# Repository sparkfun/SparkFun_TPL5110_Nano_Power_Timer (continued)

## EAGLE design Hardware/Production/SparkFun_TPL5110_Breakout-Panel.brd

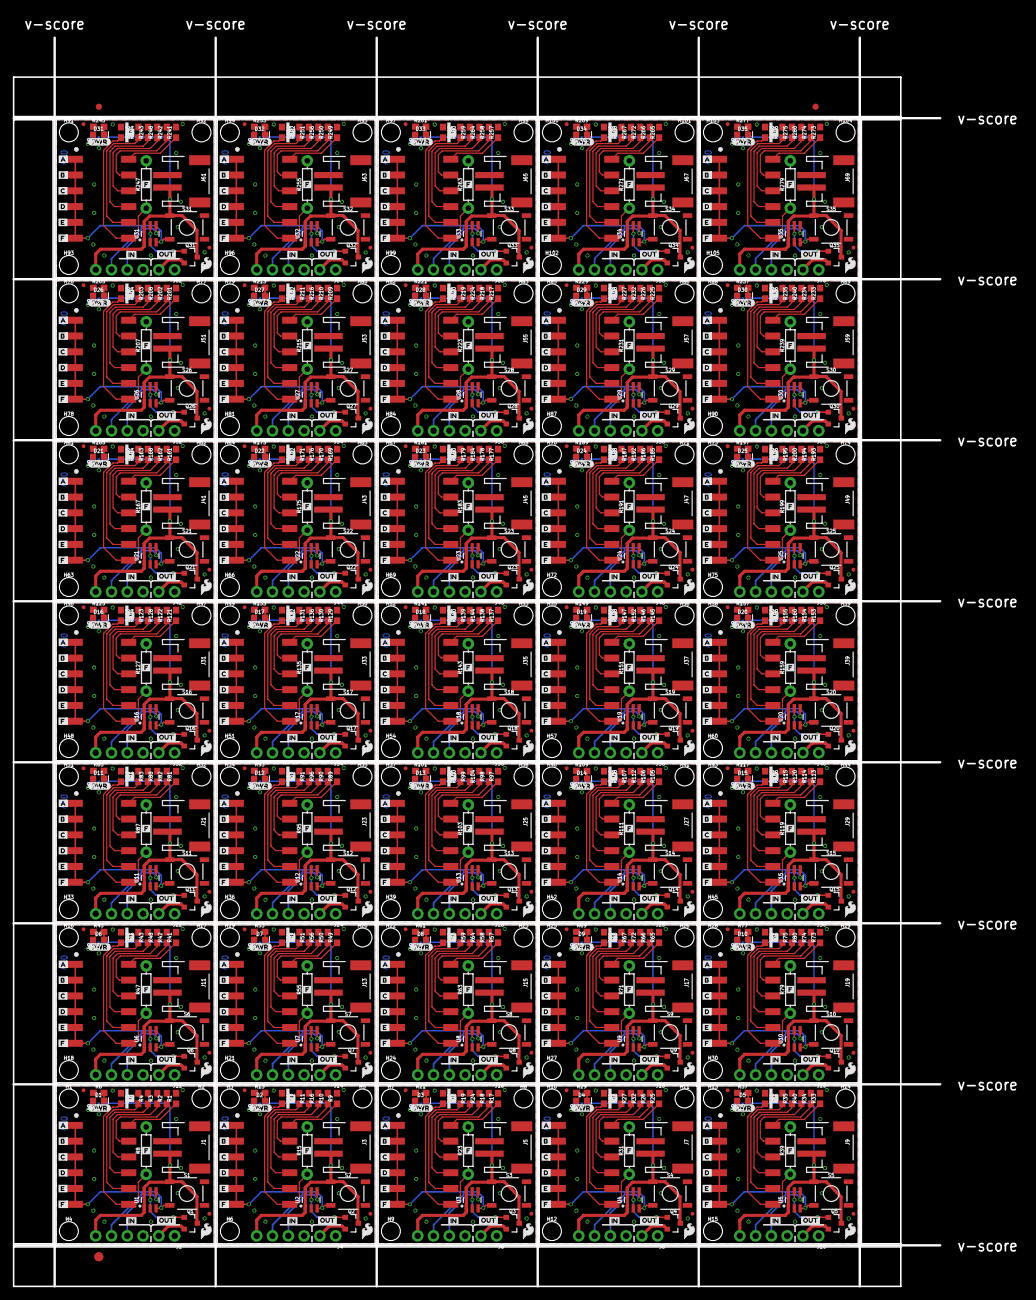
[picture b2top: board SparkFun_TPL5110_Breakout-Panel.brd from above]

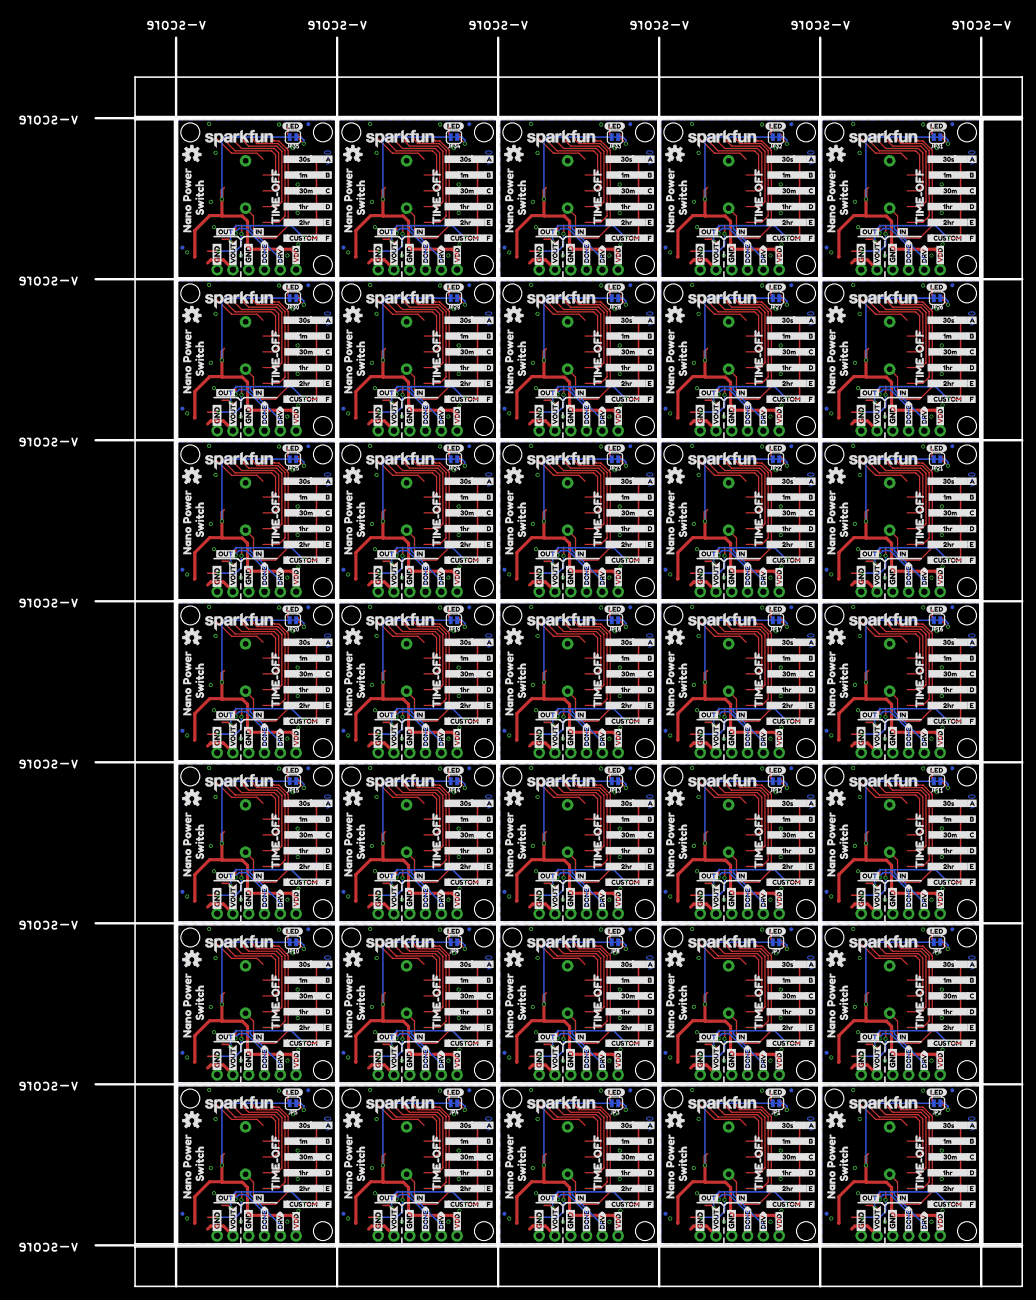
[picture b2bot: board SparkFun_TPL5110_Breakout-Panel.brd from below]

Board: 2 copper layers, 149.1 x 200.9 mm, 2138 parts (1015 on the bottom side), 490 nets.

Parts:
D1, D2, D3, D4, D5, D6, D7, D8, D9, D10, D11, D12, D13, D14, D15, D16, D17, D18, D19, D20, D21, D22, D23, D24, D25, D26, D27, D28, D29, D30, D31, D32, D33, D34, D35: RED; LED-0603
E$1, E$2: FIDUCIAL-1X2
E$3: FIDUCIAL-1.5X3
FD1, FD2, FD3, FD4, FD5, FD6, FD7, FD8, FD9, FD10, FD11, FD12, FD13, FD14, FD15, FD16, FD17, FD18, FD19, FD20, FD21, FD22, FD23, FD24, FD25, FD26, FD27, FD28, FD29, FD30, FD31, FD32, FD33, FD34, FD35, FD36, FD37, FD38, FD39, FD40, FD41, FD42, FD43, FD44, FD45, FD46, FD47, FD48, FD49, FD50, FD51, FD52, FD53, FD54, FD55, FD56, FD57, FD58, FD59, FD60, FD61, FD62, FD63, FD64, FD65, FD66, FD67, FD68, FD69, FD70, FD71, FD72, FD73, FD74, FD75, FD76, FD77, FD78, FD79, FD80, FD81, FD82, FD83, FD84, FD85, FD86, FD87, FD88, FD89, FD90, FD91, FD92, FD93, FD94, FD95, FD96, FD97, FD98, FD99, FD100, FD101, FD102, FD103, FD104, FD105, FD106, FD107, FD108, FD109, FD110, FD111, FD112, FD113, FD114, FD115, FD116, FD117, FD118, FD119, FD120, FD121, FD122, FD123, FD124, FD125, FD126, FD127, FD128, FD129, FD130, FD131, FD132, FD133, FD134, FD135, FD136, FD137, FD138, FD139, FD140: FIDUCIALUFIDUCIAL; FIDUCIAL-MICRO
H1, H2, H3, H4, H5, H6, H7, H8, H9, H10, H11, H12, H13, H14, H15, H16, H17, H18, H19, H20, H21, H22, H23, H24, H25, H26, H27, H28, H29, H30, H31, H32, H33, H34, H35, H36, H37, H38, H39, H40, H41, H42, H43, H44, H45, H46, H47, H48, H49, H50, H51, H52, H53, H54, H55, H56, H57, H58, H59, H60, H61, H62, H63, H64, H65, H66, H67, H68, H69, H70, H71, H72, H73, H74, H75, H76, H77, H78, H79, H80, H81, H82, H83, H84, H85, H86, H87, H88, H89, H90, H91, H92, H93, H94, H95, H96, H97, H98, H99, H100, H101, H102, H103, H104, H105: STAND-OFFTIGHT; STAND-OFF-TIGHT
J1, J3, J5, J7, J9, J11, J13, J15, J17, J19, J21, J23, J25, J27, J29, J31, J33, J35, J37, J39, J41, J43, J45, J47, J49, J51, J53, J55, J57, J59, J61, J63, J65, J67, J69: JST-2-SMD
J2, J4, J6, J8, J10, J12, J14, J16, J18, J20, J22, J24, J26, J28, J30, J32, J34, J36, J38, J40, J42, J44, J46, J48, J50, J52, J54, J56, J58, J60, J62, J64, J66, J68, J70: 1X06_NO_SILK
JP1, JP2, JP3, JP4, JP5, JP6, JP7, JP8, JP9, JP10, JP11, JP12, JP13, JP14, JP15, JP16, JP17, JP18, JP19, JP20, JP21, JP22, JP23, JP24, JP25, JP26, JP27, JP28, JP29, JP30, JP31, JP32, JP33, JP34, JP35: LED; SMT-JUMPER_2_NC_TRACE_SILK
LOGO1, LOGO4, LOGO7, LOGO10, LOGO13, LOGO16, LOGO19, LOGO22, LOGO25, LOGO28, LOGO31, LOGO34, LOGO37, LOGO40, LOGO43, LOGO46, LOGO49, LOGO52, LOGO55, LOGO58, LOGO61, LOGO64, LOGO67, LOGO70, LOGO73, LOGO76, LOGO79, LOGO82, LOGO85, LOGO88, LOGO91, LOGO94, LOGO97, LOGO100, LOGO103: SFE_LOGO_NAME.1_INCH; SFE_LOGO_NAME_.1
LOGO2, LOGO5, LOGO8, LOGO11, LOGO14, LOGO17, LOGO20, LOGO23, LOGO26, LOGO29, LOGO32, LOGO35, LOGO38, LOGO41, LOGO44, LOGO47, LOGO50, LOGO53, LOGO56, LOGO59, LOGO62, LOGO65, LOGO68, LOGO71, LOGO74, LOGO77, LOGO80, LOGO83, LOGO86, LOGO89, LOGO92, LOGO95, LOGO98, LOGO101, LOGO104: OSHW-LOGOS; OSHW-LOGO-S
LOGO3, LOGO6, LOGO9, LOGO12, LOGO15, LOGO18, LOGO21, LOGO24, LOGO27, LOGO30, LOGO33, LOGO36, LOGO39, LOGO42, LOGO45, LOGO48, LOGO51, LOGO54, LOGO57, LOGO60, LOGO63, LOGO66, LOGO69, LOGO72, LOGO75, LOGO78, LOGO81, LOGO84, LOGO87, LOGO90, LOGO93, LOGO96, LOGO99, LOGO102, LOGO105: SFE_LOGO_FLAME.1_INCH; SFE_LOGO_FLAME_.1
Q1, Q2, Q3, Q4, Q5, Q6, Q7, Q8, Q9, Q10, Q11, Q12, Q13, Q14, Q15, Q16, Q17, Q18, Q19, Q20, Q21, Q22, Q23, Q24, Q25, Q26, Q27, Q28, Q29, Q30, Q31, Q32, Q33, Q34, Q35: 1.1A/60V/600mΩ; SOT23-3
R1, R9, R17, R25, R33, R41, R49, R57, R65, R73, R81, R89, R97, R105, R113, R121, R129, R137, R145, R153, R161, R169, R177, R185, R193, R201, R209, R217, R225, R233, R241, R249, R257, R265, R273: 16.2k; 0603
R2, R10, R18, R26, R34, R42, R50, R58, R66, R74, R82, R90, R98, R106, R114, R122, R130, R138, R146, R154, R162, R170, R178, R186, R194, R202, R210, R218, R226, R234, R242, R250, R258, R266, R274: 22k; 0603
R3, R16, R24, R32, R40, R48, R56, R64, R72, R80, R88, R96, R104, R112, R120, R128, R136, R144, R152, R160, R168, R176, R184, R192, R200, R208, R216, R224, R232, R240, R248, R256, R264, R272, R280: 93.1k; 0603
R4, R11, R19, R27, R35, R43, R51, R59, R67, R75, R83, R91, R99, R107, R115, R123, R131, R139, R147, R155, R163, R171, R179, R187, R195, R203, R211, R219, R227, R235, R243, R251, R259, R267, R275: 124k; 0603
R5, R12, R20, R28, R36, R44, R52, R60, R68, R76, R84, R92, R100, R108, R116, R124, R132, R140, R148, R156, R164, R172, R180, R188, R196, R204, R212, R220, R228, R236, R244, R252, R260, R268, R276: 169K; 0603
R6, R13, R21, R29, R37, R45, R53, R61, R69, R77, R85, R93, R101, R109, R117, R125, R133, R141, R149, R157, R165, R173, R181, R189, R197, R205, R213, R221, R229, R237, R245, R253, R261, R269, R277: 330; 0603
R7, R14, R22, R30, R38, R46, R54, R62, R70, R78, R86, R94, R102, R110, R118, R126, R134, R142, R150, R158, R166, R174, R182, R190, R198, R206, R214, R222, R230, R238, R246, R254, R262, R270, R278: 0603
R8, R15, R23, R31, R39, R47, R55, R63, R71, R79, R87, R95, R103, R111, R119, R127, R135, R143, R151, R159, R167, R175, R183, R191, R199, R207, R215, R223, R231, R239, R247, R255, R263, R271, R279: AXIAL-0.3
S1, S2, S3, S4, S5, S6, S7, S8, S9, S10, S11, S12, S13, S14, S15, S16, S17, S18, S19, S20, S21, S22, S23, S24, S25, S26, S27, S28, S29, S30, S31, S32, S33, S34, S35: MOMENTARY-SWITCH-SPST-SMD-5.2MM-TALL; TACTILE_SWITCH_SMD_5.2MM
SW1, SW2, SW3, SW4, SW5, SW6, SW7, SW8, SW9, SW10, SW11, SW12, SW13, SW14, SW15, SW16, SW17, SW18, SW19, SW20, SW21, SW22, SW23, SW24, SW25, SW26, SW27, SW28, SW29, SW30, SW31, SW32, SW33, SW34, SW35: DIP-06; DIPSWITCH-06-SMD
U1, U2, U3, U4, U5, U6, U7, U8, U9, U10, U11, U12, U13, U14, U15, U16, U17, U18, U19, U20, U21, U22, U23, U24, U25, U26, U27, U28, U29, U30, U31, U32, U33, U34, U35: TPL5110; SOT23-6
U$1, U$42, U$77, U$112, U$147, U$182, U$217, U$252, U$287, U$322, U$357, U$392, U$427, U$462, U$497, U$532, U$567, U$602, U$637, U$672, U$707, U$742, U$777, U$812, U$847, U$882, U$917, U$952, U$987, U$1022, U$1057, U$1092, U$1127, U$1162, U$1197: DONE0
U$2, U$4, U$36, U$38, U$71, U$73, U$106, U$108, U$141, U$143, U$176, U$178, U$211, U$213, U$246, U$248, U$281, U$283, U$316, U$318, U$351, U$353, U$386, U$388, U$421, U$423, U$456, U$458, U$491, U$493, U$526, U$528, U$561, U$563, U$596, U$598, U$631, U$633, U$666, U$668, U$701, U$703, U$736, U$738, U$771, U$773, U$806, U$808, U$841, U$843, U$876, U$878, U$911, U$913, U$946, U$948, U$981, U$983, U$1016, U$1018, U$1051, U$1053, U$1086, U$1088, U$1121, U$1123, U$1156, U$1158, U$1191, U$1193: GND-03
U$3, U$43, U$78, U$113, U$148, U$183, U$218, U$253, U$288, U$323, U$358, U$393, U$428, U$463, U$498, U$533, U$568, U$603, U$638, U$673, U$708, U$743, U$778, U$813, U$848, U$883, U$918, U$953, U$988, U$1023, U$1058, U$1093, U$1128, U$1163, U$1198: VOUT0
U$5, U$37, U$72, U$107, U$142, U$177, U$212, U$247, U$282, U$317, U$352, U$387, U$422, U$457, U$492, U$527, U$562, U$597, U$632, U$667, U$702, U$737, U$772, U$807, U$842, U$877, U$912, U$947, U$982, U$1017, U$1052, U$1087, U$1122, U$1157, U$1192: VDD0
U$6, U$68, U$103, U$138, U$173, U$208, U$243, U$278, U$313, U$348, U$383, U$418, U$453, U$488, U$523, U$558, U$593, U$628, U$663, U$698, U$733, U$768, U$803, U$838, U$873, U$908, U$943, U$978, U$1013, U$1048, U$1083, U$1118, U$1153, U$1188, U$1223: NANO_POWER0
U$7, U$69, U$104, U$139, U$174, U$209, U$244, U$279, U$314, U$349, U$384, U$419, U$454, U$489, U$524, U$559, U$594, U$629, U$664, U$699, U$734, U$769, U$804, U$839, U$874, U$909, U$944, U$979, U$1014, U$1049, U$1084, U$1119, U$1154, U$1189, U$1224: SWITCH0
U$8, U$59, U$94, U$129, U$164, U$199, U$234, U$269, U$304, U$339, U$374, U$409, U$444, U$479, U$514, U$549, U$584, U$619, U$654, U$689, U$724, U$759, U$794, U$829, U$864, U$899, U$934, U$969, U$1004, U$1039, U$1074, U$1109, U$1144, U$1179, U$1214: 1M0
U$9, U$63, U$98, U$133, U$168, U$203, U$238, U$273, U$308, U$343, U$378, U$413, U$448, U$483, U$518, U$553, U$588, U$623, U$658, U$693, U$728, U$763, U$798, U$833, U$868, U$903, U$938, U$973, U$1008, U$1043, U$1078, U$1113, U$1148, U$1183, U$1218: 30S4
U$10, U$60, U$95, U$130, U$165, U$200, U$235, U$270, U$305, U$340, U$375, U$410, U$445, U$480, U$515, U$550, U$585, U$620, U$655, U$690, U$725, U$760, U$795, U$830, U$865, U$900, U$935, U$970, U$1005, U$1040, U$1075, U$1110, U$1145, U$1180, U$1215: 30M2
U$11, U$61, U$96, U$131, U$166, U$201, U$236, U$271, U$306, U$341, U$376, U$411, U$446, U$481, U$516, U$551, U$586, U$621, U$656, U$691, U$726, U$761, U$796, U$831, U$866, U$901, U$936, U$971, U$1006, U$1041, U$1076, U$1111, U$1146, U$1181, U$1216: 1HR3
U$12, U$62, U$97, U$132, U$167, U$202, U$237, U$272, U$307, U$342, U$377, U$412, U$447, U$482, U$517, U$552, U$587, U$622, U$657, U$692, U$727, U$762, U$797, U$832, U$867, U$902, U$937, U$972, U$1007, U$1042, U$1077, U$1112, U$1147, U$1182, U$1217: 2HR4
U$13, U$40, U$75, U$110, U$145, U$180, U$215, U$250, U$285, U$320, U$355, U$390, U$425, U$460, U$495, U$530, U$565, U$600, U$635, U$670, U$705, U$740, U$775, U$810, U$845, U$880, U$915, U$950, U$985, U$1020, U$1055, U$1090, U$1125, U$1160, U$1195: LED0
U$14, U$39, U$74, U$109, U$144, U$179, U$214, U$249, U$284, U$319, U$354, U$389, U$424, U$459, U$494, U$529, U$564, U$599, U$634, U$669, U$704, U$739, U$774, U$809, U$844, U$879, U$914, U$949, U$984, U$1019, U$1054, U$1089, U$1124, U$1159, U$1194: CUSTOM0
U$15, U$41, U$76, U$111, U$146, U$181, U$216, U$251, U$286, U$321, U$356, U$391, U$426, U$461, U$496, U$531, U$566, U$601, U$636, U$671, U$706, U$741, U$776, U$811, U$846, U$881, U$916, U$951, U$986, U$1021, U$1056, U$1091, U$1126, U$1161, U$1196: TIME#OFF0
U$16, U$44, U$79, U$114, U$149, U$184, U$219, U$254, U$289, U$324, U$359, U$394, U$429, U$464, U$499, U$534, U$569, U$604, U$639, U$674, U$709, U$744, U$779, U$814, U$849, U$884, U$919, U$954, U$989, U$1024, U$1059, U$1094, U$1129, U$1164, U$1199: DRV0
U$17, U$25, U$45, U$53, U$80, U$88, U$115, U$123, U$150, U$158, U$185, U$193, U$220, U$228, U$255, U$263, U$290, U$298, U$325, U$333, U$360, U$368, U$395, U$403, U$430, U$438, U$465, U$473, U$500, U$508, U$535, U$543, U$570, U$578, U$605, U$613, U$640, U$648, U$675, U$683, U$710, U$718, U$745, U$753, U$780, U$788, U$815, U$823, U$850, U$858, U$885, U$893, U$920, U$928, U$955, U$963, U$990, U$998, U$1025, U$1033, U$1060, U$1068, U$1095, U$1103, U$1130, U$1138, U$1165, U$1173, U$1200, U$1208: A0
U$18, U$26, U$46, U$54, U$81, U$89, U$116, U$124, U$151, U$159, U$186, U$194, U$221, U$229, U$256, U$264, U$291, U$299, U$326, U$334, U$361, U$369, U$396, U$404, U$431, U$439, U$466, U$474, U$501, U$509, U$536, U$544, U$571, U$579, U$606, U$614, U$641, U$649, U$676, U$684, U$711, U$719, U$746, U$754, U$781, U$789, U$816, U$824, U$851, U$859, U$886, U$894, U$921, U$929, U$956, U$964, U$991, U$999, U$1026, U$1034, U$1061, U$1069, U$1096, U$1104, U$1131, U$1139, U$1166, U$1174, U$1201, U$1209: B1
U$19, U$27, U$47, U$55, U$82, U$90, U$117, U$125, U$152, U$160, U$187, U$195, U$222, U$230, U$257, U$265, U$292, U$300, U$327, U$335, U$362, U$370, U$397, U$405, U$432, U$440, U$467, U$475, U$502, U$510, U$537, U$545, U$572, U$580, U$607, U$615, U$642, U$650, U$677, U$685, U$712, U$720, U$747, U$755, U$782, U$790, U$817, U$825, U$852, U$860, U$887, U$895, U$922, U$930, U$957, U$965, U$992, U$1000, U$1027, U$1035, U$1062, U$1070, U$1097, U$1105, U$1132, U$1140, U$1167, U$1175, U$1202, U$1210: C2
U$20, U$28, U$48, U$56, U$83, U$91, U$118, U$126, U$153, U$161, U$188, U$196, U$223, U$231, U$258, U$266, U$293, U$301, U$328, U$336, U$363, U$371, U$398, U$406, U$433, U$441, U$468, U$476, U$503, U$511, U$538, U$546, U$573, U$581, U$608, U$616, U$643, U$651, U$678, U$686, U$713, U$721, U$748, U$756, U$783, U$791, U$818, U$826, U$853, U$861, U$888, U$896, U$923, U$931, U$958, U$966, U$993, U$1001, U$1028, U$1036, U$1063, U$1071, U$1098, U$1106, U$1133, U$1141, U$1168, U$1176, U$1203, U$1211: D3
U$21, U$29, U$49, U$57, U$84, U$92, U$119, U$127, U$154, U$162, U$189, U$197, U$224, U$232, U$259, U$267, U$294, U$302, U$329, U$337, U$364, U$372, U$399, U$407, U$434, U$442, U$469, U$477, U$504, U$512, U$539, U$547, U$574, U$582, U$609, U$617, U$644, U$652, U$679, U$687, U$714, U$722, U$749, U$757, U$784, U$792, U$819, U$827, U$854, U$862, U$889, U$897, U$924, U$932, U$959, U$967, U$994, U$1002, U$1029, U$1037, U$1064, U$1072, U$1099, U$1107, U$1134, U$1142, U$1169, U$1177, U$1204, U$1212: E4
U$22, U$23, U$24, U$30, U$50, U$51, U$52, U$58, U$85, U$86, U$87, U$93, U$120, U$121, U$122, U$128, U$155, U$156, U$157, U$163, U$190, U$191, U$192, U$198, U$225, U$226, U$227, U$233, U$260, U$261, U$262, U$268, U$295, U$296, U$297, U$303, U$330, U$331, U$332, U$338, U$365, U$366, U$367, U$373, U$400, U$401, U$402, U$408, U$435, U$436, U$437, U$443, U$470, U$471, U$472, U$478, U$505, U$506, U$507, U$513, U$540, U$541, U$542, U$548, U$575, U$576, U$577, U$583, U$610, U$611, U$612, U$618, U$645, U$646, U$647, U$653, U$680, U$681, U$682, U$688, U$715, U$716, U$717, U$723, U$750, U$751, U$752, U$758, U$785, U$786, U$787, U$793, U$820, U$821, U$822, U$828, U$855, U$856, U$857, U$863, U$890, U$891, U$892, U$898, U$925, U$926, U$927, U$933, U$960, U$961, U$962, U$968, U$995, U$996, U$997, U$1003, U$1030, U$1031, U$1032, U$1038, U$1065, U$1066, U$1067, U$1073, U$1100, U$1101, U$1102, U$1108, U$1135, U$1136, U$1137, U$1143, U$1170, U$1171, U$1172, U$1178, U$1205, U$1206, U$1207, U$1213: F5
U$31, U$33, U$64, U$66, U$99, U$101, U$134, U$136, U$169, U$171, U$204, U$206, U$239, U$241, U$274, U$276, U$309, U$311, U$344, U$346, U$379, U$381, U$414, U$416, U$449, U$451, U$484, U$486, U$519, U$521, U$554, U$556, U$589, U$591, U$624, U$626, U$659, U$661, U$694, U$696, U$729, U$731, U$764, U$766, U$799, U$801, U$834, U$836, U$869, U$871, U$904, U$906, U$939, U$941, U$974, U$976, U$1009, U$1011, U$1044, U$1046, U$1079, U$1081, U$1114, U$1116, U$1149, U$1151, U$1184, U$1186, U$1219, U$1221: IN0
U$32, U$34, U$65, U$67, U$100, U$102, U$135, U$137, U$170, U$172, U$205, U$207, U$240, U$242, U$275, U$277, U$310, U$312, U$345, U$347, U$380, U$382, U$415, U$417, U$450, U$452, U$485, U$487, U$520, U$522, U$555, U$557, U$590, U$592, U$625, U$627, U$660, U$662, U$695, U$697, U$730, U$732, U$765, U$767, U$800, U$802, U$835, U$837, U$870, U$872, U$905, U$907, U$940, U$942, U$975, U$977, U$1010, U$1012, U$1045, U$1047, U$1080, U$1082, U$1115, U$1117, U$1150, U$1152, U$1185, U$1187, U$1220, U$1222: OUT1
U$35, U$70, U$105, U$140, U$175, U$210, U$245, U$280, U$315, U$350, U$385, U$420, U$455, U$490, U$525, U$560, U$595, U$630, U$665, U$700, U$735, U$770, U$805, U$840, U$875, U$910, U$945, U$980, U$1015, U$1050, U$1085, U$1120, U$1155, U$1190, U$1225: PWR-()-03

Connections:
!DRV: Q1.1, U1.5
!DRV1: Q2.1, U2.5
!DRV2: Q3.1, U3.5
!DRV3: Q4.1, U4.5
!DRV4: Q5.1, U5.5
!DRV5: Q6.1, U6.5
!DRV6: Q7.1, U7.5
!DRV7: Q8.1, U8.5
!DRV8: Q9.1, U9.5
!DRV9: Q10.1, U10.5
!DRV10: Q11.1, U11.5
!DRV11: Q12.1, U12.5
!DRV12: Q13.1, U13.5
!DRV13: Q14.1, U14.5
!DRV14: Q15.1, U15.5
!DRV15: Q16.1, U16.5
!DRV16: Q17.1, U17.5
!DRV17: Q18.1, U18.5
!DRV18: Q19.1, U19.5
!DRV19: Q20.1, U20.5
!DRV20: Q21.1, U21.5
!DRV21: Q22.1, U22.5
!DRV22: Q23.1, U23.5
!DRV23: Q24.1, U24.5
!DRV24: Q25.1, U25.5
!DRV25: Q26.1, U26.5
!DRV26: Q27.1, U27.5
!DRV27: Q28.1, U28.5
!DRV28: Q29.1, U29.5
!DRV29: Q30.1, U30.5
!DRV30: Q31.1, U31.5
!DRV31: Q32.1, U32.5
!DRV32: Q33.1, U33.5
!DRV33: Q34.1, U34.5
!DRV34: Q35.1, U35.5
DELAY/M_DRIVE: J2.5, S1.3, SW1.1, SW1.2, SW1.3, SW1.4, SW1.5, SW1.6, U1.3
DELAY/M_DRIVE1: J4.5, S2.3, SW2.1, SW2.2, SW2.3, SW2.4, SW2.5, SW2.6, U2.3
DELAY/M_DRIVE2: J6.5, S3.3, SW3.1, SW3.2, SW3.3, SW3.4, SW3.5, SW3.6, U3.3
DELAY/M_DRIVE3: J8.5, S4.3, SW4.1, SW4.2, SW4.3, SW4.4, SW4.5, SW4.6, U4.3
DELAY/M_DRIVE4: J10.5, S5.3, SW5.1, SW5.2, SW5.3, SW5.4, SW5.5, SW5.6, U5.3
DELAY/M_DRIVE5: J12.5, S6.3, SW6.1, SW6.2, SW6.3, SW6.4, SW6.5, SW6.6, U6.3
DELAY/M_DRIVE6: J14.5, S7.3, SW7.1, SW7.2, SW7.3, SW7.4, SW7.5, SW7.6, U7.3
DELAY/M_DRIVE7: J16.5, S8.3, SW8.1, SW8.2, SW8.3, SW8.4, SW8.5, SW8.6, U8.3
DELAY/M_DRIVE8: J18.5, S9.3, SW9.1, SW9.2, SW9.3, SW9.4, SW9.5, SW9.6, U9.3
DELAY/M_DRIVE9: J20.5, S10.3, SW10.1, SW10.2, SW10.3, SW10.4, SW10.5, SW10.6, U10.3
DELAY/M_DRIVE10: J22.5, S11.3, SW11.1, SW11.2, SW11.3, SW11.4, SW11.5, SW11.6, U11.3
DELAY/M_DRIVE11: J24.5, S12.3, SW12.1, SW12.2, SW12.3, SW12.4, SW12.5, SW12.6, U12.3
DELAY/M_DRIVE12: J26.5, S13.3, SW13.1, SW13.2, SW13.3, SW13.4, SW13.5, SW13.6, U13.3
DELAY/M_DRIVE13: J28.5, S14.3, SW14.1, SW14.2, SW14.3, SW14.4, SW14.5, SW14.6, U14.3
DELAY/M_DRIVE14: J30.5, S15.3, SW15.1, SW15.2, SW15.3, SW15.4, SW15.5, SW15.6, U15.3
DELAY/M_DRIVE15: J32.5, S16.3, SW16.1, SW16.2, SW16.3, SW16.4, SW16.5, SW16.6, U16.3
DELAY/M_DRIVE16: J34.5, S17.3, SW17.1, SW17.2, SW17.3, SW17.4, SW17.5, SW17.6, U17.3
DELAY/M_DRIVE17: J36.5, S18.3, SW18.1, SW18.2, SW18.3, SW18.4, SW18.5, SW18.6, U18.3
DELAY/M_DRIVE18: J38.5, S19.3, SW19.1, SW19.2, SW19.3, SW19.4, SW19.5, SW19.6, U19.3
DELAY/M_DRIVE19: J40.5, S20.3, SW20.1, SW20.2, SW20.3, SW20.4, SW20.5, SW20.6, U20.3
DELAY/M_DRIVE20: J42.5, S21.3, SW21.1, SW21.2, SW21.3, SW21.4, SW21.5, SW21.6, U21.3
DELAY/M_DRIVE21: J44.5, S22.3, SW22.1, SW22.2, SW22.3, SW22.4, SW22.5, SW22.6, U22.3
DELAY/M_DRIVE22: J46.5, S23.3, SW23.1, SW23.2, SW23.3, SW23.4, SW23.5, SW23.6, U23.3
DELAY/M_DRIVE23: J48.5, S24.3, SW24.1, SW24.2, SW24.3, SW24.4, SW24.5, SW24.6, U24.3
DELAY/M_DRIVE24: J50.5, S25.3, SW25.1, SW25.2, SW25.3, SW25.4, SW25.5, SW25.6, U25.3
DELAY/M_DRIVE25: J52.5, S26.3, SW26.1, SW26.2, SW26.3, SW26.4, SW26.5, SW26.6, U26.3
DELAY/M_DRIVE26: J54.5, S27.3, SW27.1, SW27.2, SW27.3, SW27.4, SW27.5, SW27.6, U27.3
DELAY/M_DRIVE27: J56.5, S28.3, SW28.1, SW28.2, SW28.3, SW28.4, SW28.5, SW28.6, U28.3
DELAY/M_DRIVE28: J58.5, S29.3, SW29.1, SW29.2, SW29.3, SW29.4, SW29.5, SW29.6, U29.3
DELAY/M_DRIVE29: J60.5, S30.3, SW30.1, SW30.2, SW30.3, SW30.4, SW30.5, SW30.6, U30.3
DELAY/M_DRIVE30: J62.5, S31.3, SW31.1, SW31.2, SW31.3, SW31.4, SW31.5, SW31.6, U31.3
DELAY/M_DRIVE31: J64.5, S32.3, SW32.1, SW32.2, SW32.3, SW32.4, SW32.5, SW32.6, U32.3
DELAY/M_DRIVE32: J66.5, S33.3, SW33.1, SW33.2, SW33.3, SW33.4, SW33.5, SW33.6, U33.3
DELAY/M_DRIVE33: J68.5, S34.3, SW34.1, SW34.2, SW34.3, SW34.4, SW34.5, SW34.6, U34.3
DELAY/M_DRIVE34: J70.5, S35.3, SW35.1, SW35.2, SW35.3, SW35.4, SW35.5, SW35.6, U35.3
DONE: J2.4, U1.4
DONE1: J4.4, U2.4
DONE2: J6.4, U3.4
DONE3: J8.4, U4.4
DONE4: J10.4, U5.4
DONE5: J12.4, U6.4
DONE6: J14.4, U7.4
DONE7: J16.4, U8.4
DONE8: J18.4, U9.4
DONE9: J20.4, U10.4
DONE10: J22.4, U11.4
DONE11: J24.4, U12.4
DONE12: J26.4, U13.4
DONE13: J28.4, U14.4
DONE14: J30.4, U15.4
DONE15: J32.4, U16.4
DONE16: J34.4, U17.4
DONE17: J36.4, U18.4
DONE18: J38.4, U19.4
DONE19: J40.4, U20.4
DONE20: J42.4, U21.4
DONE21: J44.4, U22.4
DONE22: J46.4, U23.4
DONE23: J48.4, U24.4
DONE24: J50.4, U25.4
DONE25: J52.4, U26.4
DONE26: J54.4, U27.4
DONE27: J56.4, U28.4
DONE28: J58.4, U29.4
DONE29: J60.4, U30.4
DONE30: J62.4, U31.4
DONE31: J64.4, U32.4
DONE32: J66.4, U33.4
DONE33: J68.4, U34.4
DONE34: J70.4, U35.4
GND: J1.1, J2.1, J2.3, R1.2, R2.2, R3.2, R4.2, R5.2, R6.1, R7.1, R8.P$2, U1.2
GND1: J3.1, J4.1, J4.3, R9.2, R10.2, R11.2, R12.2, R13.1, R14.1, R15.P$2, R16.2, U2.2
GND2: J5.1, J6.1, J6.3, R17.2, R18.2, R19.2, R20.2, R21.1, R22.1, R23.P$2, R24.2, U3.2
GND3: J7.1, J8.1, J8.3, R25.2, R26.2, R27.2, R28.2, R29.1, R30.1, R31.P$2, R32.2, U4.2
GND4: J9.1, J10.1, J10.3, R33.2, R34.2, R35.2, R36.2, R37.1, R38.1, R39.P$2, R40.2, U5.2
GND5: J11.1, J12.1, J12.3, R41.2, R42.2, R43.2, R44.2, R45.1, R46.1, R47.P$2, R48.2, U6.2
GND6: J13.1, J14.1, J14.3, R49.2, R50.2, R51.2, R52.2, R53.1, R54.1, R55.P$2, R56.2, U7.2
GND7: J15.1, J16.1, J16.3, R57.2, R58.2, R59.2, R60.2, R61.1, R62.1, R63.P$2, R64.2, U8.2
GND8: J17.1, J18.1, J18.3, R65.2, R66.2, R67.2, R68.2, R69.1, R70.1, R71.P$2, R72.2, U9.2
GND9: J19.1, J20.1, J20.3, R73.2, R74.2, R75.2, R76.2, R77.1, R78.1, R79.P$2, R80.2, U10.2
GND10: J21.1, J22.1, J22.3, R81.2, R82.2, R83.2, R84.2, R85.1, R86.1, R87.P$2, R88.2, U11.2
GND11: J23.1, J24.1, J24.3, R89.2, R90.2, R91.2, R92.2, R93.1, R94.1, R95.P$2, R96.2, U12.2
GND12: J25.1, J26.1, J26.3, R97.2, R98.2, R99.2, R100.2, R101.1, R102.1, R103.P$2, R104.2, U13.2
GND13: J27.1, J28.1, J28.3, R105.2, R106.2, R107.2, R108.2, R109.1, R110.1, R111.P$2, R112.2, U14.2
GND14: J29.1, J30.1, J30.3, R113.2, R114.2, R115.2, R116.2, R117.1, R118.1, R119.P$2, R120.2, U15.2
GND15: J31.1, J32.1, J32.3, R121.2, R122.2, R123.2, R124.2, R125.1, R126.1, R127.P$2, R128.2, U16.2
GND16: J33.1, J34.1, J34.3, R129.2, R130.2, R131.2, R132.2, R133.1, R134.1, R135.P$2, R136.2, U17.2
GND17: J35.1, J36.1, J36.3, R137.2, R138.2, R139.2, R140.2, R141.1, R142.1, R143.P$2, R144.2, U18.2
GND18: J37.1, J38.1, J38.3, R145.2, R146.2, R147.2, R148.2, R149.1, R150.1, R151.P$2, R152.2, U19.2
GND19: J39.1, J40.1, J40.3, R153.2, R154.2, R155.2, R156.2, R157.1, R158.1, R159.P$2, R160.2, U20.2
GND20: J41.1, J42.1, J42.3, R161.2, R162.2, R163.2, R164.2, R165.1, R166.1, R167.P$2, R168.2, U21.2
GND21: J43.1, J44.1, J44.3, R169.2, R170.2, R171.2, R172.2, R173.1, R174.1, R175.P$2, R176.2, U22.2
GND22: J45.1, J46.1, J46.3, R177.2, R178.2, R179.2, R180.2, R181.1, R182.1, R183.P$2, R184.2, U23.2
GND23: J47.1, J48.1, J48.3, R185.2, R186.2, R187.2, R188.2, R189.1, R190.1, R191.P$2, R192.2, U24.2
GND24: J49.1, J50.1, J50.3, R193.2, R194.2, R195.2, R196.2, R197.1, R198.1, R199.P$2, R200.2, U25.2
GND25: J51.1, J52.1, J52.3, R201.2, R202.2, R203.2, R204.2, R205.1, R206.1, R207.P$2, R208.2, U26.2
GND26: J53.1, J54.1, J54.3, R209.2, R210.2, R211.2, R212.2, R213.1, R214.1, R215.P$2, R216.2, U27.2
GND27: J55.1, J56.1, J56.3, R217.2, R218.2, R219.2, R220.2, R221.1, R222.1, R223.P$2, R224.2, U28.2
GND28: J57.1, J58.1, J58.3, R225.2, R226.2, R227.2, R228.2, R229.1, R230.1, R231.P$2, R232.2, U29.2
GND29: J59.1, J60.1, J60.3, R233.2, R234.2, R235.2, R236.2, R237.1, R238.1, R239.P$2, R240.2, U30.2
GND30: J61.1, J62.1, J62.3, R241.2, R242.2, R243.2, R244.2, R245.1, R246.1, R247.P$2, R248.2, U31.2
GND31: J63.1, J64.1, J64.3, R249.2, R250.2, R251.2, R252.2, R253.1, R254.1, R255.P$2, R256.2, U32.2
GND32: J65.1, J66.1, J66.3, R257.2, R258.2, R259.2, R260.2, R261.1, R262.1, R263.P$2, R264.2, U33.2
GND33: J67.1, J68.1, J68.3, R265.2, R266.2, R267.2, R268.2, R269.1, R270.1, R271.P$2, R272.2, U34.2
GND34: J69.1, J70.1, J70.3, R273.2, R274.2, R275.2, R276.2, R277.1, R278.1, R279.P$2, R280.2, U35.2
unnamed: D1.C, R6.2
unnamed: D2.C, R13.2
unnamed: R10.1, SW2.11
unnamed: R1.1, SW1.12
unnamed: R2.1, SW1.11
unnamed: R3.1, SW1.10
unnamed: R4.1, SW1.9
unnamed: R5.1, SW1.8
unnamed: R7.2, R8.P$1, SW1.7
unnamed: R16.1, SW2.10
unnamed: D1.A, JP2.1
unnamed: R14.2, R15.P$1, SW2.7
unnamed: R12.1, SW2.8
unnamed: R11.1, SW2.9
unnamed: R9.1, SW2.12
unnamed: D2.A, JP1.1
unnamed: D3.C, R21.2
unnamed: R18.1, SW3.11
unnamed: R24.1, SW3.10
unnamed: R22.2, R23.P$1, SW3.7
unnamed: R20.1, SW3.8
unnamed: R19.1, SW3.9
unnamed: R17.1, SW3.12
unnamed: D3.A, JP3.1
unnamed: D4.C, R29.2
unnamed: R26.1, SW4.11
unnamed: R32.1, SW4.10
unnamed: R30.2, R31.P$1, SW4.7
unnamed: R28.1, SW4.8
unnamed: R27.1, SW4.9
unnamed: R25.1, SW4.12
unnamed: D4.A, JP4.1
unnamed: D5.C, R37.2
unnamed: R34.1, SW5.11
unnamed: R40.1, SW5.10
unnamed: R38.2, R39.P$1, SW5.7
unnamed: R36.1, SW5.8
unnamed: R35.1, SW5.9
unnamed: R33.1, SW5.12
unnamed: D5.A, JP5.1
unnamed: D6.C, R45.2
unnamed: R42.1, SW6.11
unnamed: R48.1, SW6.10
unnamed: R46.2, R47.P$1, SW6.7
unnamed: R44.1, SW6.8
unnamed: R43.1, SW6.9
unnamed: R41.1, SW6.12
unnamed: D6.A, JP6.1
unnamed: D7.C, R53.2
unnamed: R50.1, SW7.11
unnamed: R56.1, SW7.10
unnamed: R54.2, R55.P$1, SW7.7
unnamed: R52.1, SW7.8
unnamed: R51.1, SW7.9
unnamed: R49.1, SW7.12
unnamed: D7.A, JP7.1
unnamed: D8.C, R61.2
unnamed: R58.1, SW8.11
unnamed: R64.1, SW8.10
unnamed: R62.2, R63.P$1, SW8.7
unnamed: R60.1, SW8.8
unnamed: R59.1, SW8.9
unnamed: R57.1, SW8.12
unnamed: D8.A, JP8.1
unnamed: D9.C, R69.2
unnamed: R66.1, SW9.11
unnamed: R72.1, SW9.10
unnamed: R70.2, R71.P$1, SW9.7
unnamed: R68.1, SW9.8
unnamed: R67.1, SW9.9
unnamed: R65.1, SW9.12
unnamed: D9.A, JP9.1
unnamed: D10.C, R77.2
unnamed: R74.1, SW10.11
unnamed: R80.1, SW10.10
unnamed: R78.2, R79.P$1, SW10.7
unnamed: R76.1, SW10.8
unnamed: R75.1, SW10.9
unnamed: R73.1, SW10.12
unnamed: D10.A, JP10.1
unnamed: D11.C, R85.2
unnamed: R82.1, SW11.11
unnamed: R88.1, SW11.10
unnamed: R86.2, R87.P$1, SW11.7
unnamed: R84.1, SW11.8
unnamed: R83.1, SW11.9
unnamed: R81.1, SW11.12
unnamed: D11.A, JP11.1
unnamed: D12.C, R93.2
unnamed: R90.1, SW12.11
unnamed: R96.1, SW12.10
unnamed: R94.2, R95.P$1, SW12.7
unnamed: R92.1, SW12.8
unnamed: R91.1, SW12.9
unnamed: R89.1, SW12.12
unnamed: D12.A, JP12.1
unnamed: D13.C, R101.2
unnamed: R98.1, SW13.11
unnamed: R104.1, SW13.10
unnamed: R102.2, R103.P$1, SW13.7
unnamed: R100.1, SW13.8
unnamed: R99.1, SW13.9
unnamed: R97.1, SW13.12
unnamed: D13.A, JP13.1
unnamed: D14.C, R109.2
unnamed: R106.1, SW14.11
unnamed: R112.1, SW14.10
unnamed: R110.2, R111.P$1, SW14.7
unnamed: R108.1, SW14.8
unnamed: R107.1, SW14.9
unnamed: R105.1, SW14.12
unnamed: D14.A, JP14.1
unnamed: D15.C, R117.2
unnamed: R114.1, SW15.11
unnamed: R120.1, SW15.10
unnamed: R118.2, R119.P$1, SW15.7
unnamed: R116.1, SW15.8
unnamed: R115.1, SW15.9
unnamed: R113.1, SW15.12
unnamed: D15.A, JP15.1
unnamed: D16.C, R125.2
unnamed: R122.1, SW16.11
unnamed: R128.1, SW16.10
unnamed: R126.2, R127.P$1, SW16.7
unnamed: R124.1, SW16.8
unnamed: R123.1, SW16.9
unnamed: R121.1, SW16.12
unnamed: D16.A, JP16.1
unnamed: D17.C, R133.2
unnamed: R130.1, SW17.11
unnamed: R136.1, SW17.10
unnamed: R134.2, R135.P$1, SW17.7
unnamed: R132.1, SW17.8
unnamed: R131.1, SW17.9
unnamed: R129.1, SW17.12
unnamed: D17.A, JP17.1
unnamed: D18.C, R141.2
unnamed: R138.1, SW18.11
unnamed: R144.1, SW18.10
unnamed: R142.2, R143.P$1, SW18.7
unnamed: R140.1, SW18.8
unnamed: R139.1, SW18.9
unnamed: R137.1, SW18.12
unnamed: D18.A, JP18.1
unnamed: D19.C, R149.2
unnamed: R146.1, SW19.11
unnamed: R152.1, SW19.10
unnamed: R150.2, R151.P$1, SW19.7
unnamed: R148.1, SW19.8
unnamed: R147.1, SW19.9
unnamed: R145.1, SW19.12
unnamed: D19.A, JP19.1
unnamed: D20.C, R157.2
unnamed: R154.1, SW20.11
unnamed: R160.1, SW20.10
unnamed: R158.2, R159.P$1, SW20.7
unnamed: R156.1, SW20.8
unnamed: R155.1, SW20.9
unnamed: R153.1, SW20.12
unnamed: D20.A, JP20.1
unnamed: D21.C, R165.2
unnamed: R162.1, SW21.11
unnamed: R168.1, SW21.10
unnamed: R166.2, R167.P$1, SW21.7
unnamed: R164.1, SW21.8
unnamed: R163.1, SW21.9
unnamed: R161.1, SW21.12
unnamed: D21.A, JP21.1
unnamed: D22.C, R173.2
unnamed: R170.1, SW22.11
unnamed: R176.1, SW22.10
unnamed: R174.2, R175.P$1, SW22.7
unnamed: R172.1, SW22.8
unnamed: R171.1, SW22.9
unnamed: R169.1, SW22.12
unnamed: D22.A, JP22.1
unnamed: D23.C, R181.2
unnamed: R178.1, SW23.11
unnamed: R184.1, SW23.10
unnamed: R182.2, R183.P$1, SW23.7
unnamed: R180.1, SW23.8
unnamed: R179.1, SW23.9
unnamed: R177.1, SW23.12
unnamed: D23.A, JP23.1
unnamed: D24.C, R189.2
unnamed: R186.1, SW24.11
unnamed: R192.1, SW24.10
unnamed: R190.2, R191.P$1, SW24.7
unnamed: R188.1, SW24.8
unnamed: R187.1, SW24.9
unnamed: R185.1, SW24.12
unnamed: D24.A, JP24.1
unnamed: D25.C, R197.2
unnamed: R194.1, SW25.11
unnamed: R200.1, SW25.10
unnamed: R198.2, R199.P$1, SW25.7
unnamed: R196.1, SW25.8
unnamed: R195.1, SW25.9
unnamed: R193.1, SW25.12
unnamed: D25.A, JP25.1
unnamed: D26.C, R205.2
unnamed: R202.1, SW26.11
unnamed: R208.1, SW26.10
unnamed: R206.2, R207.P$1, SW26.7
unnamed: R204.1, SW26.8
unnamed: R203.1, SW26.9
unnamed: R201.1, SW26.12
unnamed: D26.A, JP26.1
unnamed: D27.C, R213.2
unnamed: R210.1, SW27.11
unnamed: R216.1, SW27.10
unnamed: R214.2, R215.P$1, SW27.7
unnamed: R212.1, SW27.8
unnamed: R211.1, SW27.9
unnamed: R209.1, SW27.12
unnamed: D27.A, JP27.1
unnamed: D28.C, R221.2
unnamed: R218.1, SW28.11
unnamed: R224.1, SW28.10
unnamed: R222.2, R223.P$1, SW28.7
unnamed: R220.1, SW28.8
unnamed: R219.1, SW28.9
unnamed: R217.1, SW28.12
unnamed: D28.A, JP28.1
unnamed: D29.C, R229.2
unnamed: R226.1, SW29.11
unnamed: R232.1, SW29.10
unnamed: R230.2, R231.P$1, SW29.7
unnamed: R228.1, SW29.8
unnamed: R227.1, SW29.9
unnamed: R225.1, SW29.12
unnamed: D29.A, JP29.1
unnamed: D30.C, R237.2
unnamed: R234.1, SW30.11
unnamed: R240.1, SW30.10
unnamed: R238.2, R239.P$1, SW30.7
unnamed: R236.1, SW30.8
unnamed: R235.1, SW30.9
unnamed: R233.1, SW30.12
unnamed: D30.A, JP30.1
unnamed: D31.C, R245.2
unnamed: R242.1, SW31.11
unnamed: R248.1, SW31.10
unnamed: R246.2, R247.P$1, SW31.7
unnamed: R244.1, SW31.8
unnamed: R243.1, SW31.9
unnamed: R241.1, SW31.12
unnamed: D31.A, JP31.1
unnamed: D32.C, R253.2
unnamed: R250.1, SW32.11
unnamed: R256.1, SW32.10
unnamed: R254.2, R255.P$1, SW32.7
unnamed: R252.1, SW32.8
unnamed: R251.1, SW32.9
unnamed: R249.1, SW32.12
unnamed: D32.A, JP32.1
unnamed: D33.C, R261.2
unnamed: R258.1, SW33.11
unnamed: R264.1, SW33.10
unnamed: R262.2, R263.P$1, SW33.7
unnamed: R260.1, SW33.8
unnamed: R259.1, SW33.9
unnamed: R257.1, SW33.12
unnamed: D33.A, JP33.1
unnamed: D34.C, R269.2
unnamed: R266.1, SW34.11
unnamed: R272.1, SW34.10
unnamed: R270.2, R271.P$1, SW34.7
unnamed: R268.1, SW34.8
unnamed: R267.1, SW34.9
unnamed: R265.1, SW34.12
unnamed: D34.A, JP34.1
unnamed: D35.C, R277.2
unnamed: R274.1, SW35.11
unnamed: R280.1, SW35.10
unnamed: R278.2, R279.P$1, SW35.7
unnamed: R276.1, SW35.8
unnamed: R275.1, SW35.9
unnamed: R273.1, SW35.12
unnamed: D35.A, JP35.1
VDD: J1.2, J2.6, JP2.2, Q1.3, S1.1, U1.1, U1.6
VDD1: J3.2, J4.6, JP1.2, Q2.3, S2.1, U2.1, U2.6
VDD2: J5.2, J6.6, JP3.2, Q3.3, S3.1, U3.1, U3.6
VDD3: J7.2, J8.6, JP4.2, Q4.3, S4.1, U4.1, U4.6
VDD4: J9.2, J10.6, JP5.2, Q5.3, S5.1, U5.1, U5.6
VDD5: J11.2, J12.6, JP6.2, Q6.3, S6.1, U6.1, U6.6
VDD6: J13.2, J14.6, JP7.2, Q7.3, S7.1, U7.1, U7.6
VDD7: J15.2, J16.6, JP8.2, Q8.3, S8.1, U8.1, U8.6
VDD8: J17.2, J18.6, JP9.2, Q9.3, S9.1, U9.1, U9.6
VDD9: J19.2, J20.6, JP10.2, Q10.3, S10.1, U10.1, U10.6
VDD10: J21.2, J22.6, JP11.2, Q11.3, S11.1, U11.1, U11.6
VDD11: J23.2, J24.6, JP12.2, Q12.3, S12.1, U12.1, U12.6
VDD12: J25.2, J26.6, JP13.2, Q13.3, S13.1, U13.1, U13.6
VDD13: J27.2, J28.6, JP14.2, Q14.3, S14.1, U14.1, U14.6
VDD14: J29.2, J30.6, JP15.2, Q15.3, S15.1, U15.1, U15.6
VDD15: J31.2, J32.6, JP16.2, Q16.3, S16.1, U16.1, U16.6
VDD16: J33.2, J34.6, JP17.2, Q17.3, S17.1, U17.1, U17.6
VDD17: J35.2, J36.6, JP18.2, Q18.3, S18.1, U18.1, U18.6
VDD18: J37.2, J38.6, JP19.2, Q19.3, S19.1, U19.1, U19.6
VDD19: J39.2, J40.6, JP20.2, Q20.3, S20.1, U20.1, U20.6
VDD20: J41.2, J42.6, JP21.2, Q21.3, S21.1, U21.1, U21.6
VDD21: J43.2, J44.6, JP22.2, Q22.3, S22.1, U22.1, U22.6
VDD22: J45.2, J46.6, JP23.2, Q23.3, S23.1, U23.1, U23.6
VDD23: J47.2, J48.6, JP24.2, Q24.3, S24.1, U24.1, U24.6
VDD24: J49.2, J50.6, JP25.2, Q25.3, S25.1, U25.1, U25.6
VDD25: J51.2, J52.6, JP26.2, Q26.3, S26.1, U26.1, U26.6
VDD26: J53.2, J54.6, JP27.2, Q27.3, S27.1, U27.1, U27.6
VDD27: J55.2, J56.6, JP28.2, Q28.3, S28.1, U28.1, U28.6
VDD28: J57.2, J58.6, JP29.2, Q29.3, S29.1, U29.1, U29.6
VDD29: J59.2, J60.6, JP30.2, Q30.3, S30.1, U30.1, U30.6
VDD30: J61.2, J62.6, JP31.2, Q31.3, S31.1, U31.1, U31.6
VDD31: J63.2, J64.6, JP32.2, Q32.3, S32.1, U32.1, U32.6
VDD32: J65.2, J66.6, JP33.2, Q33.3, S33.1, U33.1, U33.6
VDD33: J67.2, J68.6, JP34.2, Q34.3, S34.1, U34.1, U34.6
VDD34: J69.2, J70.6, JP35.2, Q35.3, S35.1, U35.1, U35.6
VDD_OUT: J2.2, Q1.2
VDD_OUT1: J4.2, Q2.2
VDD_OUT2: J6.2, Q3.2
VDD_OUT3: J8.2, Q4.2
VDD_OUT4: J10.2, Q5.2
VDD_OUT5: J12.2, Q6.2
VDD_OUT6: J14.2, Q7.2
VDD_OUT7: J16.2, Q8.2
VDD_OUT8: J18.2, Q9.2
VDD_OUT9: J20.2, Q10.2
VDD_OUT10: J22.2, Q11.2
VDD_OUT11: J24.2, Q12.2
VDD_OUT12: J26.2, Q13.2
VDD_OUT13: J28.2, Q14.2
VDD_OUT14: J30.2, Q15.2
VDD_OUT15: J32.2, Q16.2
VDD_OUT16: J34.2, Q17.2
VDD_OUT17: J36.2, Q18.2
VDD_OUT18: J38.2, Q19.2
VDD_OUT19: J40.2, Q20.2
VDD_OUT20: J42.2, Q21.2
VDD_OUT21: J44.2, Q22.2
VDD_OUT22: J46.2, Q23.2
VDD_OUT23: J48.2, Q24.2
VDD_OUT24: J50.2, Q25.2
VDD_OUT25: J52.2, Q26.2
VDD_OUT26: J54.2, Q27.2
VDD_OUT27: J56.2, Q28.2
VDD_OUT28: J58.2, Q29.2
VDD_OUT29: J60.2, Q30.2
VDD_OUT30: J62.2, Q31.2
VDD_OUT31: J64.2, Q32.2
VDD_OUT32: J66.2, Q33.2
VDD_OUT33: J68.2, Q34.2
VDD_OUT34: J70.2, Q35.2

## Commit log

2019-05-06 Completes schematic and board design, adds buzzard labels
2019-05-06 Updates buzzard labels, changes 5 pin header to 6 pin
2019-05-06 Adds additional labels to switches, increases trace width of VDD
2019-05-06 Adds bare file of resistor calculator script for determining delay
2019-05-06 Adds some bare functions to resistor_calculator function
2019-05-07 Alignes swtich silk, adds "in/out" silk, increases size of product name silk
2019-05-07 Adds final resistor values: 93.1k, 124k, 169k, Updates python script so that user can calculate combinations with 6th custom resistor
2019-05-07 Adds Production Files and adds text to custom resistors
2019-05-08 Moves Production Files to main file structure, updates board file and resistor calculator readme
2019-05-08 Renames boad and schematic files to avoid confusion
2019-05-15 Switches gate and source nets, attaches LED to VDD_OUT, adds "+" and "-" silk to board
2019-06-04 New Buzzard Label
    Adjusted buzzard labels, moved flash chip down a hair so it isn't on top of the JST
2019-06-10 Update Firmware Examples
    - Separate TPL5110 Python Script from Arduino examples
    - Add example used in tutorial to toggle TPL5110's Done pin
2019-06-10 Update TPL5110_Blink_Done_Example.ino
    Add note
2019-07-16 Fixes image in README
2019-07-16 Tries to do what last commit was supposed to do
2019-07-16 Removes resistance calculator
